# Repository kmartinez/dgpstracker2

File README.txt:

Computer Science dissertation project by Emily James
University of SOuthampton, April 2021
pyb - files that should be flashed or copied onto the microcontrollers
client - code run separately on a PC

More advanced version of picogps project - using ublox dGPS and a pyboard with lcd screen for local checks/config.

We will be using docstring to properly document each section of code better optimisation and future development & 
reference.

Any general modifications will be made through using Visual Studio Code connected directly to the board. 
These changes will then be copied over to this working repository for better reference.

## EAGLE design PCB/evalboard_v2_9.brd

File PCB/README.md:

### Issues found on version 1 of evalboard:
- P-channel MOSFETs Q1, Q3, Q5 are in reverse direction
- Outputs of BQ24074 are not isolated from input of LTC3130-1 and LTC3113
- Battery 2mm JST footprint requires special Sparkfun sockets
- Solar input header does not fit standard 3.5mm screw terminals
- PJ-031D is the wrong way around (facing the inside of the board)
- PJ-031D solar input jack is not long enough, but otherwise locks into the solar connector OK
- VS1 and VS2 of LTC3130-1 is the other way around (GND and VCC) giving 5V instead of 3.3V
- Signal names create confusion

### Improvements/additions in next version:
- [x] Fix the direction of Q1, Q3, Q5
- [x] Isolate BQ24074 output from the input of LTC3130-1 and LTC3113
- [x] Remove JST battery terminal
- [x] Swap Solar input screw terminal footprint with a ~~standard~~ push-click one
- [x] Make PJ-031D face away from board
- [x] Swap VS1 and VS2
- [x] Rename ambiguous signal names
- [x] Power tracks width increased from 10 to 16 mil, where appropriate
- [x] Added more pins for input/output signals for probing when jumpered
- [x] Added two more outputs: 
  - one for 5V GSM
  -  one for 3.3V GSM logic
- [x] Added two versions of power switches for consumption comparison:
  - one with DMG/DMP mosfets
  - one with ~~DMC3028LSDX-13~~ IRF7319 dual cmos
- [x] Add pads for Harwin RFI cans 
	- 30mm X 30mm or 50mm X 25mm for LTC3113 section 
	- 30mm X 25mm for LTC3130-1 section

### Ordered:
- DMG3414U N-channel MOSFET - unavailable at mouser!
- DMP2045U P-channel MOSFET
- IRF7319 Dual P/N-channel MOSFET pair

### Notes/remaining issues:
-  Harwin RFI can pads are only there for future design reference,
 the dimensions of the latest version's pads are not compatible with any of the available models

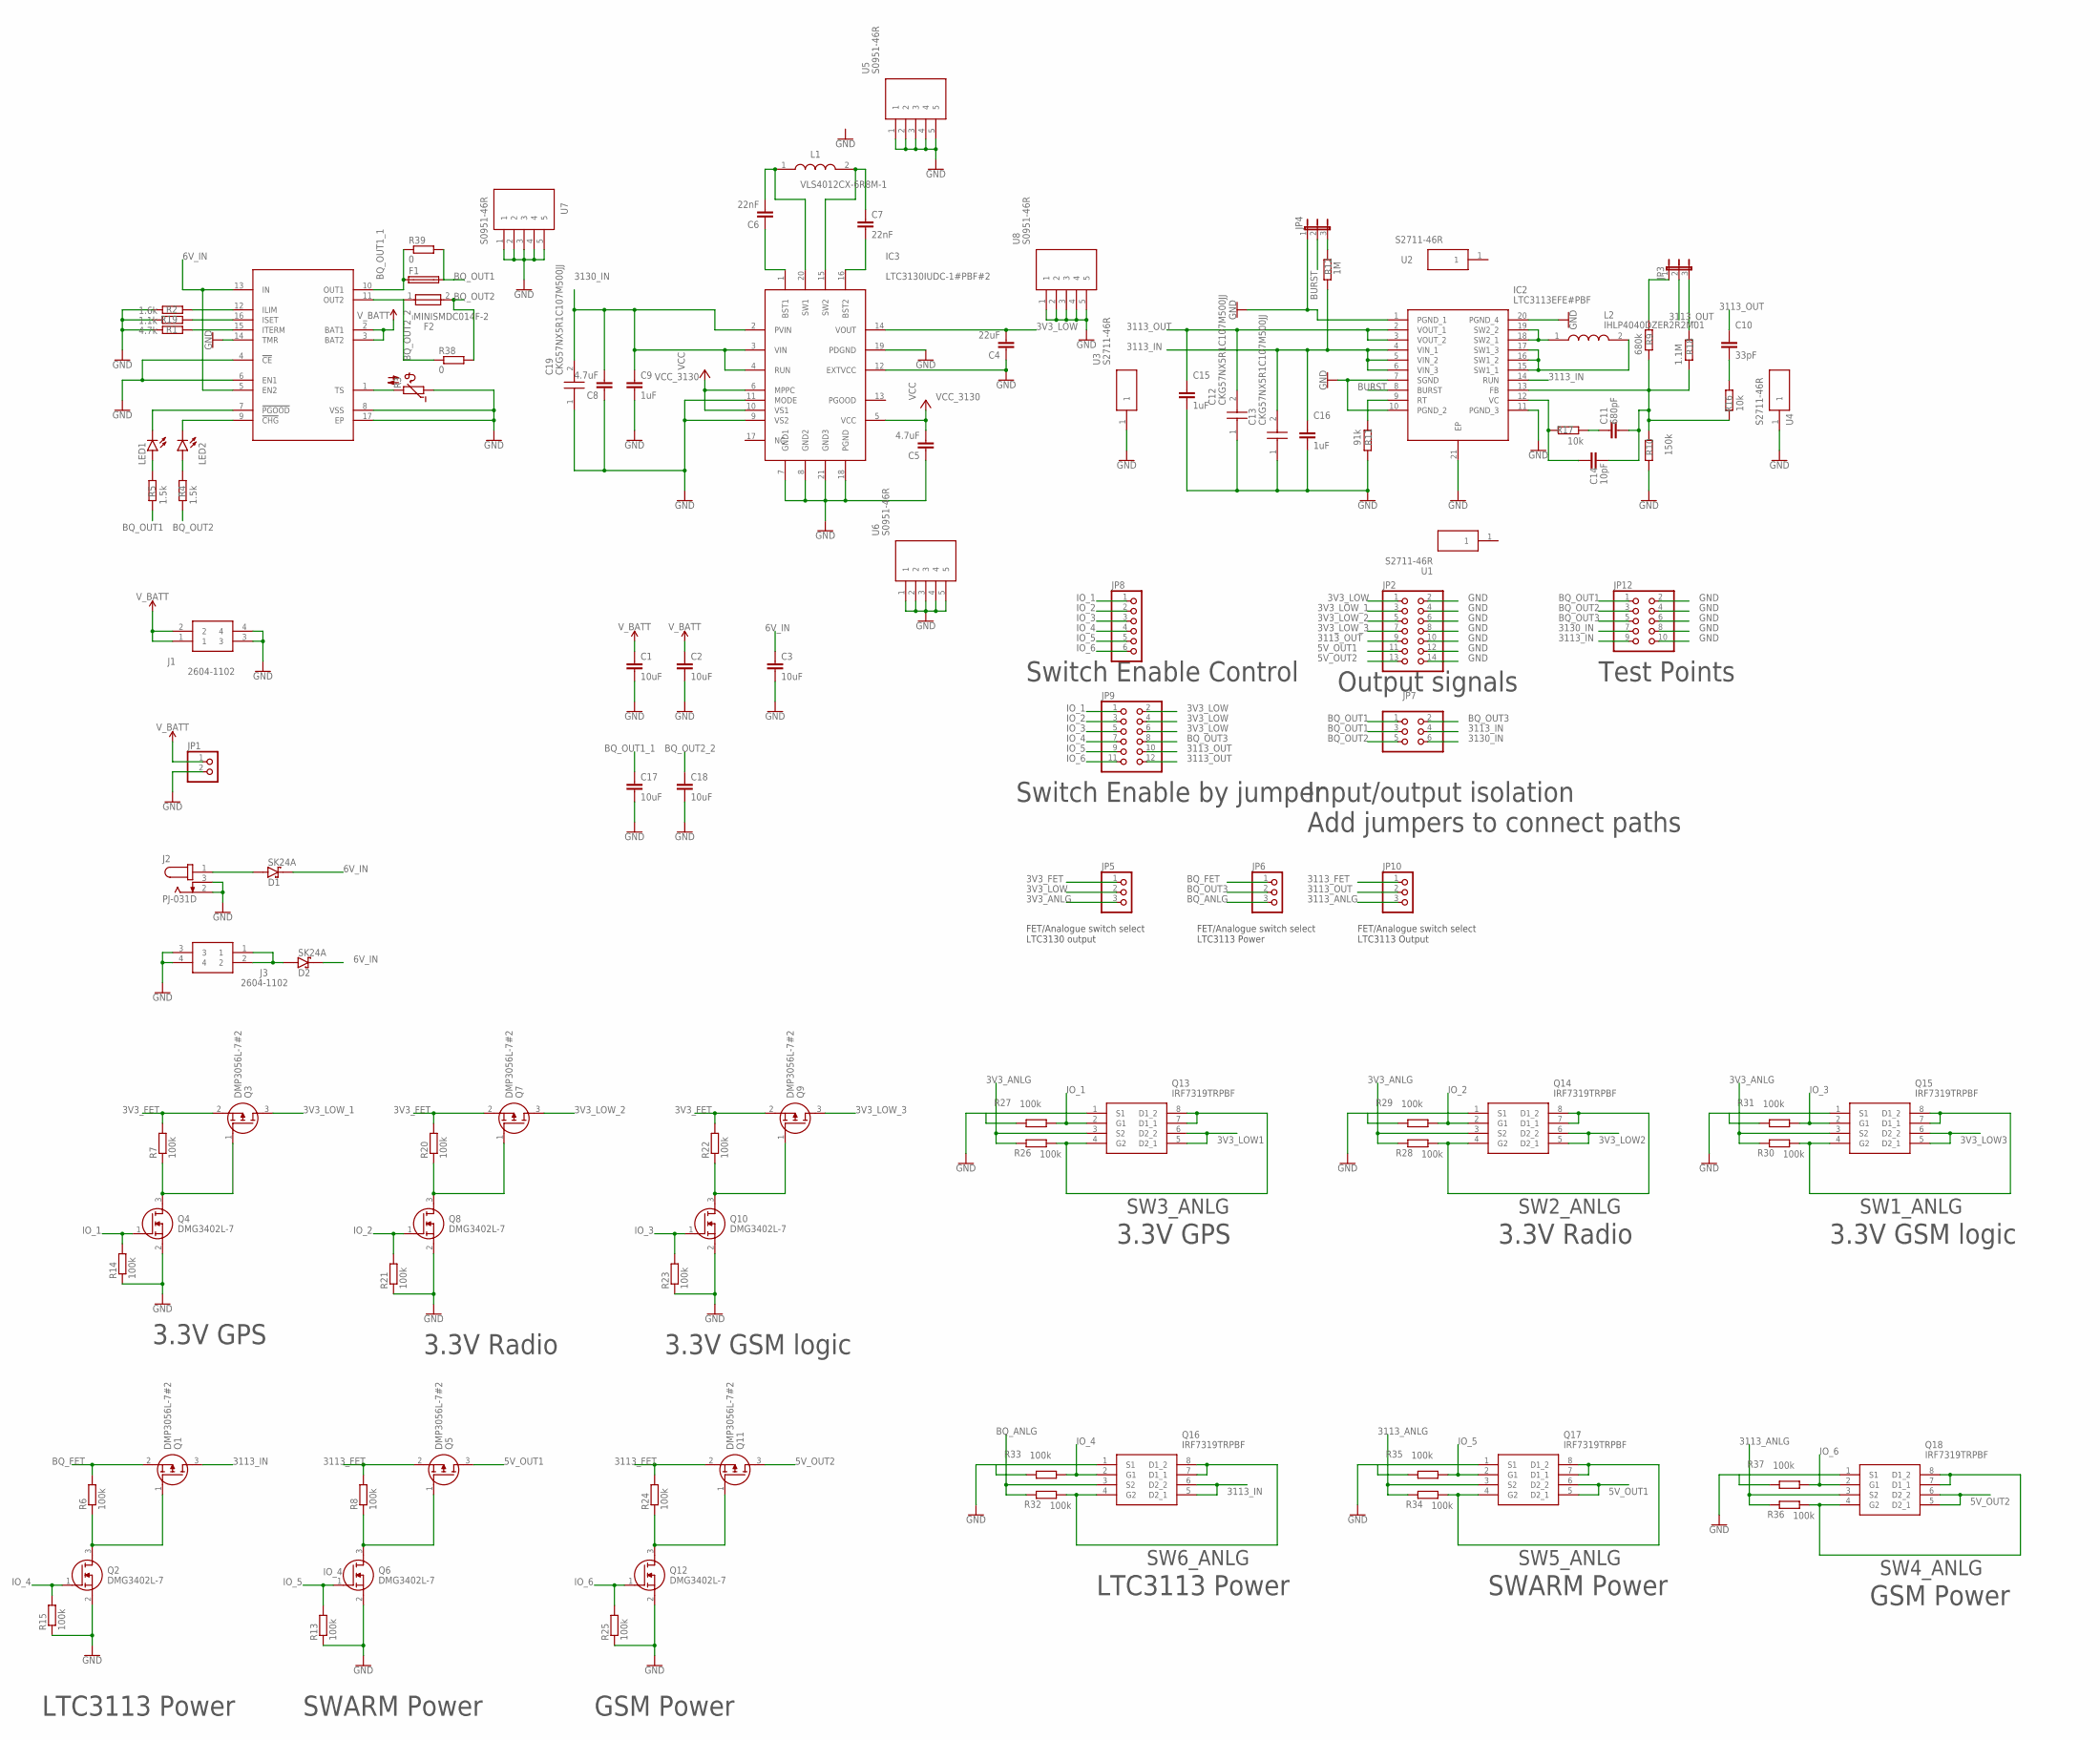
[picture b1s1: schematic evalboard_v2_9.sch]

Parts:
C1, C2, C3, C17, C18: 10uF; C1210
C4: 22uF; C1210
C5, C8: 4.7uF; C1210
C6, C7: 22nF; C0603
C9, C15, C16: 1uF; C0603
C10: 33pF; C0603
C11: 680pF; C0603
C12, C13, C19: CKG57NX5R1C107M500JJ; CAPC6050X550N
C14: 10pF; C0603
D1, D2: SK24A; DIOM4325X250N
F1: MF-USHT150KX-2SMD; 1210
F2: MINISMDC014F-2; FUSSC455X324X89-2N
IC1: BQ24074; QFN50P300X300X100-17N
IC2: LTC3113EFE#PBF; SOP65P640X120-21N
IC3: LTC3130IUDC-1#PBF#2; QFN50P300X400X80-21N
J1, J3: 2604-1102; 26041102
J2: PJ-031D; CUI_PJ-031D
JP1: PINHD-1X2; 1X02
JP2: PINHD-2X7; 2X07
JP3, JP4: JP2E; JP2
JP5, JP6, JP10: PINHD-1X3; 1X03
JP7: PINHD-2X3; 2X03
JP8: PINHD-1X6; 1X06
JP9: PINHD-2X6; 2X06
JP12: PINHD-2X5; 2X05
L1: VLS4012CX-6R8M-1; VLS4012
L2: IHLP4040DZER2R2M01; INDPM108102X400N
LED1, LED2: LEDCHIP-LED0603; CHIP-LED0603
Q1, Q3, Q5, Q7, Q9, Q11: DMP3056L-7#2; SOT96P240X100-3N
Q2, Q4, Q6, Q8, Q10, Q12: DMG3402L-7; SOT96P240X110-3N
Q13, Q14, Q15, Q16, Q17, Q18: IRF7319TRPBF; SOIC127P600X175-8N
R1: 4.7k; R0603
R2: 1.6k; R0603
R3: 10k; P640
R4, R5: 1.5k; R0603
R6, R7, R8, R13, R14, R15, R20, R21, R22, R23, R24, R25, R26, R27, R28, R29, R30, R31, R32, R33, R34, R35, R36, R37: 100k; R0603
R9: 680k; R0603
R10: 150k; R0603
R11: 91k; R0603
R12: 1M; R0603
R16, R17: 10k; R0603
R18: 1.1M; R0603
R19: 1.1k; R0603
R38, R39: 0; R0603
U1, U2, U3, U4: S2711-46R; S271146R
U5, U6, U7, U8: S0951-46R; S095146R

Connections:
3V3_ANLG: JP5.3, Q13.3 (S2), Q14.3 (S2), Q15.3 (S2), R26.2, R28.2, R30.2
3V3_FET: JP5.1, Q3.2 (S), Q7.2 (S), Q9.2 (S), R7.2, R20.2, R22.2
3V3_LOW: C4.2, IC3.14 (VOUT), JP2.1, JP5.2, JP9.2, JP9.4, JP9.6
3V3_LOW1: Q13.5 (D2_1), Q13.6 (D2_2)
3V3_LOW2: Q14.5 (D2_1), Q14.6 (D2_2)
3V3_LOW3: Q15.5 (D2_1), Q15.6 (D2_2)
3V3_LOW_1: JP2.3, Q3.3 (D)
3V3_LOW_2: JP2.5, Q7.3 (D)
3V3_LOW_3: JP2.7, Q9.3 (D)
5V_OUT1: JP2.11, Q5.3 (D), Q17.5 (D2_1), Q17.6 (D2_2)
5V_OUT2: JP2.13, Q11.3 (D), Q18.5 (D2_1), Q18.6 (D2_2)
6V_IN: C3.1, D1.C (K), D2.C (K), IC1.5 (EN2), IC1.13 (IN)
3113_ANLG: JP10.3, Q17.3 (S2), Q18.3 (S2), R34.2, R36.2
3113_FET: JP10.1, Q5.2 (S), Q11.2 (S), R8.2, R24.2
3113_IN: C13.2, C16.1, IC2.4 (VIN_1), IC2.5 (VIN_2), IC2.6 (VIN_3), IC2.14 (RUN), JP7.4, JP12.9, Q1.3 (D), Q16.5 (D2_1), Q16.6 (D2_2), R12.1
3113_OUT: C10.1, C12.2, C15.1, IC2.2 (VOUT_1), IC2.3 (VOUT_2), JP2.9, JP3.2, JP9.10, JP9.12, JP10.2
3130_IN: C8.2, C9.1, C19.2, IC3.2 (PVIN), IC3.3 (VIN), IC3.4 (RUN), JP7.6, JP12.7
BQ_ANLG: JP6.3, Q16.3 (S2), R32.2
BQ_FET: JP6.1, Q1.2 (S), R6.2
BQ_OUT1: F1.2, JP7.1, JP7.3, JP12.1, R5.2, R39.2
BQ_OUT1_1: C17.1, F1.1, IC1.10 (OUT1), R39.1
BQ_OUT2: F2.2, JP7.5, JP12.3, R4.2, R38.2
BQ_OUT2_2: C18.1, F2.1, IC1.11 (OUT2), R38.1
BQ_OUT3: JP6.2, JP7.2, JP9.8, JP12.5
BURST: IC2.8 (BURST), JP4.2
GND: C1.2, C2.2, C3.2, C4.1, C5.1, C8.1, C9.2, C12.1, C13.1, C15.2, C16.2, C17.2, C18.2, C19.1, IC1.4 (!CE!), IC1.6 (EN1), IC1.8 (VSS), IC1.14 (TMR), IC1.17 (EP), IC2.1 (PGND_1), IC2.7 (SGND), IC2.10 (PGND_2), IC2.11 (PGND_3), IC2.20 (PGND_4), IC2.21 (EP), IC3.7 (GND1), IC3.8 (GND2), IC3.9 (VS2), IC3.11 (MODE), IC3.12 (EXTVCC), IC3.18 (PGND), IC3.19 (PDGND), IC3.21 (GND3), J1.3, J1.4, J2.2, J2.3, J3.3, J3.4, JP1.2, JP2.2, JP2.4, JP2.6, JP2.8, JP2.10, JP2.12, JP2.14, JP4.1, JP12.2, JP12.4, JP12.6, JP12.8, JP12.10, Q2.2 (S), Q4.2 (S), Q6.2 (S), Q8.2 (S), Q10.2 (S), Q12.2 (S), Q13.1 (S1), Q14.1 (S1), Q15.1 (S1), Q16.1 (S1), Q17.1 (S1), Q18.1 (S1), R1.2, R2.2, R3.1, R10.1, R11.1, R13.1, R14.1, R15.1, R19.2, R21.1, R23.1, R25.1, U3.1, U4.1, U5.1, U5.2, U5.3, U5.4, U5.5, U6.1, U6.2, U6.3, U6.4, U6.5, U7.1, U7.2, U7.3, U7.4, U7.5, U8.1, U8.2, U8.3, U8.4, U8.5
IO_1: JP8.1, JP9.1, Q4.1 (G), Q13.2 (G1), R14.2, R27.1, R27.2, R29.2, R31.2, R33.2, R35.2, R37.2
IO_2: JP8.2, JP9.3, Q8.1 (G), Q14.2 (G1), R21.2, R29.1
IO_3: JP8.3, JP9.5, Q10.1 (G), Q15.2 (G1), R23.2, R31.1
IO_4: JP8.4, JP9.7, Q2.1 (G), Q16.2 (G1), R15.2, R33.1
IO_5: JP8.5, JP9.9, Q6.1 (G), Q17.2 (G1), R13.2, R35.1
IO_6: JP8.6, JP9.11, Q12.1 (G), Q18.2 (G1), R25.2, R37.1
unnamed: IC1.15 (ITERM), R1.1
unnamed: IC1.12 (ILIM), R2.1
unnamed: IC1.9 (!CHG!), LED2.C
unnamed: IC1.1 (TS), R3.2
unnamed: IC1.7 (!PGOOD!), LED1.C
unnamed: LED1.A, R5.1
unnamed: LED2.A, R4.1
unnamed: Q3.1 (G), Q4.3 (D), R7.1
unnamed: D1.A, J2.1
unnamed: Q1.1 (G), Q2.3 (D), R6.1
unnamed: Q5.1 (G), Q6.3 (D), R8.1
unnamed: IC2.18 (SW2_1), IC2.19 (SW2_2), L2.1
unnamed: IC2.15 (SW1_1), IC2.16 (SW1_2), IC2.17 (SW1_3), L2.2
unnamed: JP3.3, R18.2
unnamed: C6.2, IC3.20 (SW1), L1.1
unnamed: C6.1, IC3.1 (BST1)
unnamed: C7.2, IC3.16 (BST2)
unnamed: IC2.9 (RT), R11.2
unnamed: C7.1, IC3.15 (SW2), L1.2
unnamed: JP4.3, R12.2
unnamed: C11.1, R17.1
unnamed: C10.2, R16.1
unnamed: C11.2, C14.2, IC2.13 (FB), R9.1, R10.2, R16.2, R18.1
unnamed: C14.1, IC2.12 (VC), R17.2
unnamed: IC1.16 (ISET), R19.1
unnamed: JP3.1, R9.2
unnamed: Q7.1 (G), Q8.3 (D), R20.1
unnamed: Q9.1 (G), Q10.3 (D), R22.1
unnamed: Q11.1 (G), Q12.3 (D), R24.1
unnamed: Q14.4 (G2), Q14.7 (D1_1), Q14.8 (D1_2), R28.1
unnamed: Q15.4 (G2), Q15.7 (D1_1), Q15.8 (D1_2), R30.1
unnamed: Q16.4 (G2), Q16.7 (D1_1), Q16.8 (D1_2), R32.1
unnamed: Q17.4 (G2), Q17.7 (D1_1), Q17.8 (D1_2), R34.1
unnamed: Q13.4 (G2), Q13.7 (D1_1), Q13.8 (D1_2), R26.1
unnamed: Q18.4 (G2), Q18.7 (D1_1), Q18.8 (D1_2), R36.1
unnamed: D2.A, J3.1, J3.2
VCC_3130: C5.2, IC3.5 (VCC), IC3.6 (MPPC), IC3.10 (VS1)
V_BATT: C1.1, C2.1, IC1.2 (BAT1), IC1.3 (BAT2), J1.1, J1.2, JP1.1

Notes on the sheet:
3.3V GSM logic
3.3V Radio
3.3V GPS
LTC3113 Power
SWARM Power
GSM Power
Input/output isolation Add jumpers to connect paths
Switch Enable by jumper
Switch Enable Control
Output signals
FET/Analogue switch select LTC3130 output
FET/Analogue switch select LTC3113 Power
FET/Analogue switch select LTC3113 Output
SW1_ANLG
SW2_ANLG
SW3_ANLG
SW6_ANLG
SW5_ANLG
SW4_ANLG
Test Points

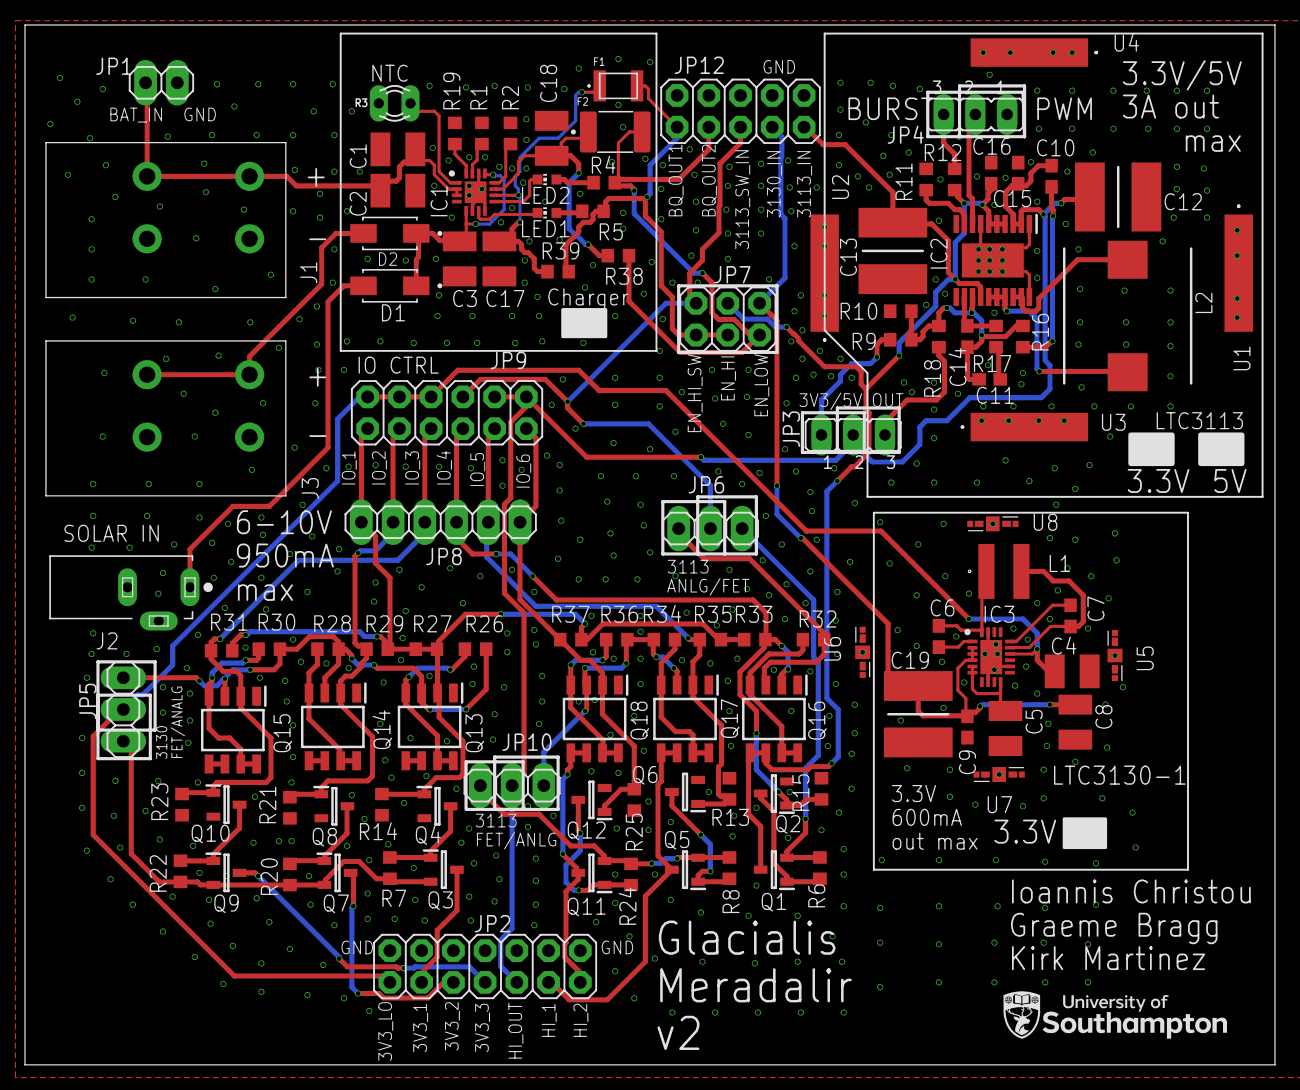
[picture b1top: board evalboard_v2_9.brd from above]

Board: 2 copper layers, 100.1 x 83.2 mm, 109 parts (0 on the bottom side), 70 nets.

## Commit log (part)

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2021-01-09 reformatted code to neaten file structure added Radio.py to process radio messages (experimental) temporarily overridden main.py in both boards to test radio conversation added extra files to aid wit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
2021-01-21 Added ECEF distance calculation in preparation for accuracy tests
2021-01-21 fixed bug caused by auto-refactoring
2021-03-01 Used custom LCD API to add screens for settings display and SVIN settings and trigger (no callback yet). Fixed bugs in screen updates that caused the pen colours to be incorrectly set.
2021-03-06 Defined concrete log class/IDs, backed up old log system
2021-03-06 Added padBytes() function and error tolerance to encode/decode functions
2021-03-06 Created binary log formats matching self-defined spec "log codes.txt" and unparser
2021-03-06 Fixed bug causing single bytes to be parsed as integers rather than bytes
2021-03-21 Copied compile/main.py to customise execution slightly for base station
2021-03-21 Added JSON configurations, Error, Event and Location Logs, Error avoidance and transmit (untested) functionality
2021-03-30 Cleaned code to remove unused functions
2021-03-30 Added time update to acceptable event logs
2021-04-13 Code cleaned
2021-04-13 Changed pAcc to be in cm rather than m
2021-04-13 Added helper function to write binary data to given file, changed incoming long-range transmission to go into a single file, datalog.bin. Fixed file reading to stop memory errors when loading large f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
2021-04-13 Changed startup timer to allow sub-hour accuracy. Changed LCD update to use last execution time rather than fixed delay. LEDs now show debug (g=fix,r=nofix,b=dgnss), and used dgpsUsed flag to determi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
2021-04-27 Final format used in code archive. Crude README for rough explanations. JSON config examples (used in demo) added.
2022-07-15 Added Protocol_test.py - Focuses on testing a simple one-pager, by confirming that data is coming into the gps uart and can be written to the radio uart. The pollMessages function verifies that gps m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
2022-07-15 New test file
2022-07-18 Modification to Protocol_test.py - Debugging session on general operation of pollMessages() and writeToRadio(). Current operation behaves okay-ish but will to consider using different uart ports. We'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
2022-07-22 First comments
2022-07-26 Amendments to support Surveying-In and Saving Configuration
    - Moved some of Emily's code that supports starting/stopping surveying-in and also added a saveCFG function to allow us to stop the base module from reverting to a rover configuration.
2022-07-27 Test files created for configuring base and rover operation.
    Currently, general operation of page forwarder works to some extent. Need to go outside and test incoming messages from rover and parse the contents to be able to get a 'Fix' and send it back to the 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
2022-07-29 Modifications to rover_test.py
    - Brainstorming ideas on what to expect for general tests prior to going outside. Currently, I wrote a couple of lines that forward the incoming radio_uart data to a PACKET_MANAGER buffer which will 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
2022-07-29 Provided TODOs for base file and created a copy of rover_test
    - This is to test if corrections can be received and forwarded to the gps uart. Afterwards, the code will retrieve nmea messages from the gps_uart on the rover and then process everything and pass it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
2022-08-02 Fully operational page forwarder communicating between both pyboards and gps boards.
    - Will need to do some cleaning up by removing some comments
    - General operation works though. RTCM Messages are sent and written to the gps_uart on the rover via the radio uart. The messages are then parsed using the nmea functions from gps.py.
    - Multiple checks are undergone before they are attempted to be send back to the base radio uart. We can finally see some useful information received from the base.
2022-08-05 Modified rover_test_corrections.py & gps.py
    - Fixed Bugs pertaining to incoming inconsistent GNGGA messages. Also added a few functions for saving configurations.
    - Provided an extra function to scan for any GNZDA messages to return the time.
2022-08-05 Fixed Errors with rover_test_corrections.py
    - imported Formats.py
    - renamed uart variable name to support gps_uart
2022-08-05 Modified base-test.py and gps.py
    - Just cleaning up some redundant code gps.py
    - Updated base-test to include Surveying-in functions and Saving Configurations from Emily's Code.
2022-08-05 Extra Comment on additional Functions for Survey-in
    Blocks of comments for original functions have been intentionally commented until a solution can be found to try rewrite these functions without having to use the LCD.
2022-08-07 Updated rover_test_corrections.py with lists of fix_types
    - Current format of detecting when the rover has a fix on its position and sends that back to the base hasn't been fully implemented correctly. Need to figure out the fix_type linked to the list and 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
2022-08-09 Quick changes to gps.py to check for FIX_QUALITY
    - Provided a reference link to the quality types that we should be looking out for
    - base will be reading any incoming messages, verifying using a checksum that it's in the right format, then send an ACK back to the rover.
2022-08-24 New GSM test code
2022-08-24 small update to AT commands
2022-08-25 Functional HTTP POST to ptsv2.com dump
2022-08-31 Added SWARM satellite pass checker
2022-09-01 Added PCB files and http hive test
2022-09-01 post to evalkit success
2022-09-08 Added issues + improvements in next ver.
2022-09-09 Added evalboard v2 with minor changes
2022-09-09 Fixed MOSFETs, VS1, VS2, updated README
2022-09-09 Updated additions in README
2022-09-22 Added schematic pdf
2022-10-14 Fixed Bugs for rover_test.py and gps.py
    nmealon2lon() and nmealat2lat() have been reviewed and resolved to return values up to 7 decimals. Currently, the operation works significantly better, taking less than 30s to start from cold boot, a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
2022-10-21 Modifications made to allow RTC get updated via GPS time. Difference is roughly about 20s, however it is inconsistent due to using decode() but that can be reviewed and rewritten in a different forma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
2022-10-22 added some comments and a function call which will be used for updating the incoming gps_messages in order to update the onboard RTC.
2022-10-28 Adding current progress, previous istory available on private GitLab
2022-10-28 Created Readme.md with TODO list
2022-10-28 Added NMEA pasring and stream for NMEA data
2022-10-28 Added removal of roveres from ack_list after ack is sent
2022-10-28 Convert Device and Base to modules instead of classes to avoid double instantiation, among other refactors
2022-11-02 Added debug comments and libs ready for testing
2022-11-02 Remove enum import (probably fine)
2022-11-03 Corrected pin assignements, added debug to ASYNC functions, changed GPS parser
2022-11-03 Emmended ASYNC
2022-11-03 Properly fix serialize
2022-11-03 Install pyrtcm lib
2022-11-03 Change deserialize checksum to crc
2022-11-03 misc debugging 1
2022-11-04 Begin moving drivers to their own folder
2022-11-04 Move sending and receiving to radio driver
2022-11-04 Remove old radio code
2022-11-04 Bugfix
2022-11-04 Make radio send and receive packet gud
2022-11-07 Remove .vscode folder
2022-11-07 add .vscode to gitignore
2022-11-07 get rid of UART_TESTING
2022-11-08 add config for time between alarms
2022-11-08 add some utility python files for setup
2022-11-09 Bugfixing
2022-11-10 LARGE day of work - RTCM3 now works, had incorrect packet ident - Added avergaing and SD checking for NEMA response - Need to fix fix qualty indicator
2022-11-17 Updated some of the docstrings
2022-11-21 modifying code structure - created separate directories for filesystem, radio-system and general source code from original pyb.
2022-11-21 modified README - just extra edits about how the code structure will be like in this branch.
2022-11-21 moved all files from filesystem to radio-system directory.
2022-11-21 modified main loop to detect when button's pressed in sync with LED for better interfacing.
2022-11-21 AsyncUART refactor. Behaves more like normal UART
2022-11-21 make adafruit_gps less custom (parsing bugfix still applies)
2022-11-21 New Math folder for math related things. Moved standard deviation, etc. to there
2022-11-21 watered-down numpy exists so we use that
2022-11-21 Backup code for filesystem testing. Will attempt to slowly add snippets to get the filesystem bit of the code working.
2022-11-21 Filesystem code integrated successfully into ThingPlus. Added comments using DocString for better reference. Hopefully should be useful for the system.
2022-11-22 Modified Filesystem code to write the correct formatted data - just need to make sure they are tabulated correctly.
2022-11-24 Removed redundant code snippet. Currently looking into how to fix the RTC by preventing it from resetting.
2022-11-24 Working on displaying real-time data using displayio. Currently displaying just a simple text on screen but the goal will be to have real-time data show up and update.
2022-11-24 Change some super()s to selfs
2022-11-24 stop binning gps lines
2022-11-28 re-add utility stats functions
2022-11-28 rename adafruit_gps
2022-11-28 Made GPS not terrible
2022-11-30 Massively untested code for ingestion
2022-12-01 Sorted rover loop. Serialisation needs work
2022-12-05 new debug setting
2022-12-05 debug fake gps data
2022-12-05 no pycache pls
2022-12-05 additional log and config change
2022-12-05 bugfix on ack receive
2022-12-05 config consistency upgrade
2022-12-06 Updated system to run in display mode whilst being able to write to the filesystem using Pin D12 and a push button. Code being backed-up.
2022-12-06 logging and bugfix default config changed for dev purposes
2022-12-06 message format changes
2022-12-07 gps config change
2022-12-07 logging
2022-12-08 added sutdowns
2022-12-08 added alarm thing
2022-12-08 Added radio checksum debug
2022-12-09 bubble up checksum errors to avoid deadlocks
2022-12-09 asyncio shenanigans because timeouts suck
2022-12-09 fix hdop
2022-12-09 we don't need rts/cts after upping radio buffer
2022-12-09 mega debug
2022-12-11 api works over http
2022-12-13 Added RTC timestamp updates and file access
2022-12-14 Filesystem changes, modifications to many functions. Needs reset
2022-12-14 Revert "Filesystem changes, modifications to many functions. Needs reset"
    This reverts commit 0d6451e2205dc4594ac62d74e6a8a7d81075db77.
2022-12-14 initial move to file-based data logging
2022-12-14 Data logging attempt 2 use separate files
2022-12-14 RTC calibration and setting
2022-12-14 UBX-CFG update for base for RTC times
2022-12-14 watchdog and gsm manual enable
2022-12-15 watchdog reset detection
2022-12-15 Add watchdog disable
2022-12-15 make gps update return bool
2022-12-15 logging overhaul
2022-12-15 Minor changes to make work :)
2022-12-15 set internal time source to RTC
2022-12-20 Just making sure all files are committed - need to include gitignore
2023-01-04 docstrings
2023-01-11 Make sphinx actually function
2023-01-11 stop adding built docs to git
2023-01-11 more sensible docstrings
2023-01-11 fix docstring typos
2023-01-11 Remove accidental duplicate
2023-01-11 Add rest of src folders to docs
2023-01-12 Docs building readme
2023-01-18 Test code for current measurement using INA219, ATH20 and AQZ202 switch
2023-01-19 Fixed bugs and added a few lines to control switch using GPIO pin 12 on Feather. Currently works.
2023-01-20 Added ability to write data to filesystem. Need to get this fully integrated where a packet is posted once data has been appended to the file.
2023-01-23 Modified data logger to write data to the filesystem and attempt to post data to the server. Currently stuck on a simple bug, but will reattempt posting.
2023-01-23 Code Refactoring and cleaning up.
2023-01-23 Code requires cleaning up, but posting and writing to the filesystem fully works.

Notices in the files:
parts and their libraries:
SparkFun-PowerSymbols: Licensing: Creative Commons ShareAlike 4.0 International - https://creativecommons.org/licenses/by-sa/4.0
